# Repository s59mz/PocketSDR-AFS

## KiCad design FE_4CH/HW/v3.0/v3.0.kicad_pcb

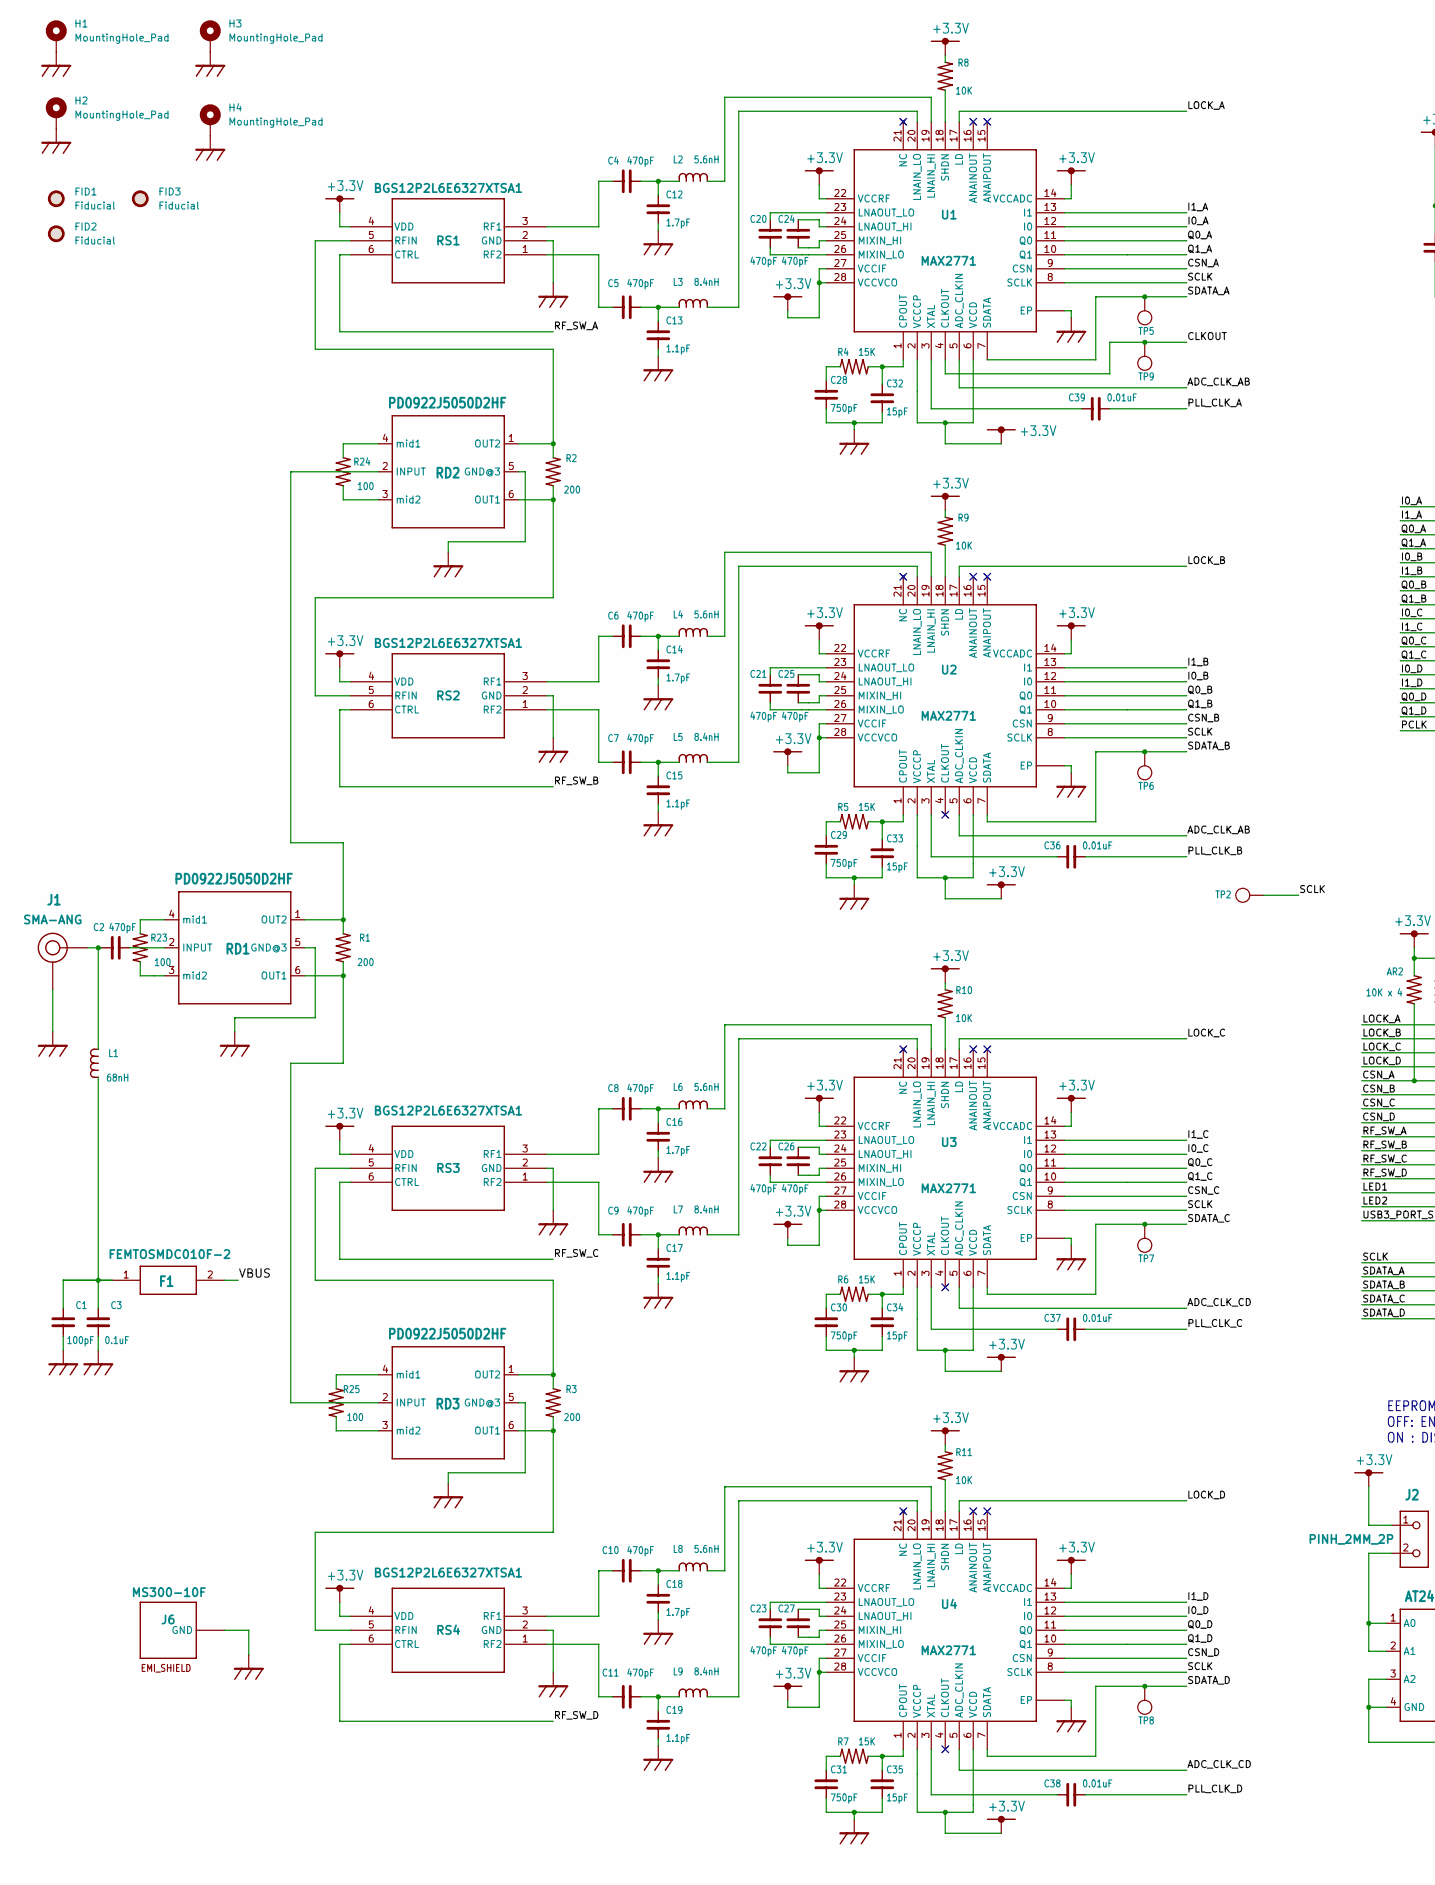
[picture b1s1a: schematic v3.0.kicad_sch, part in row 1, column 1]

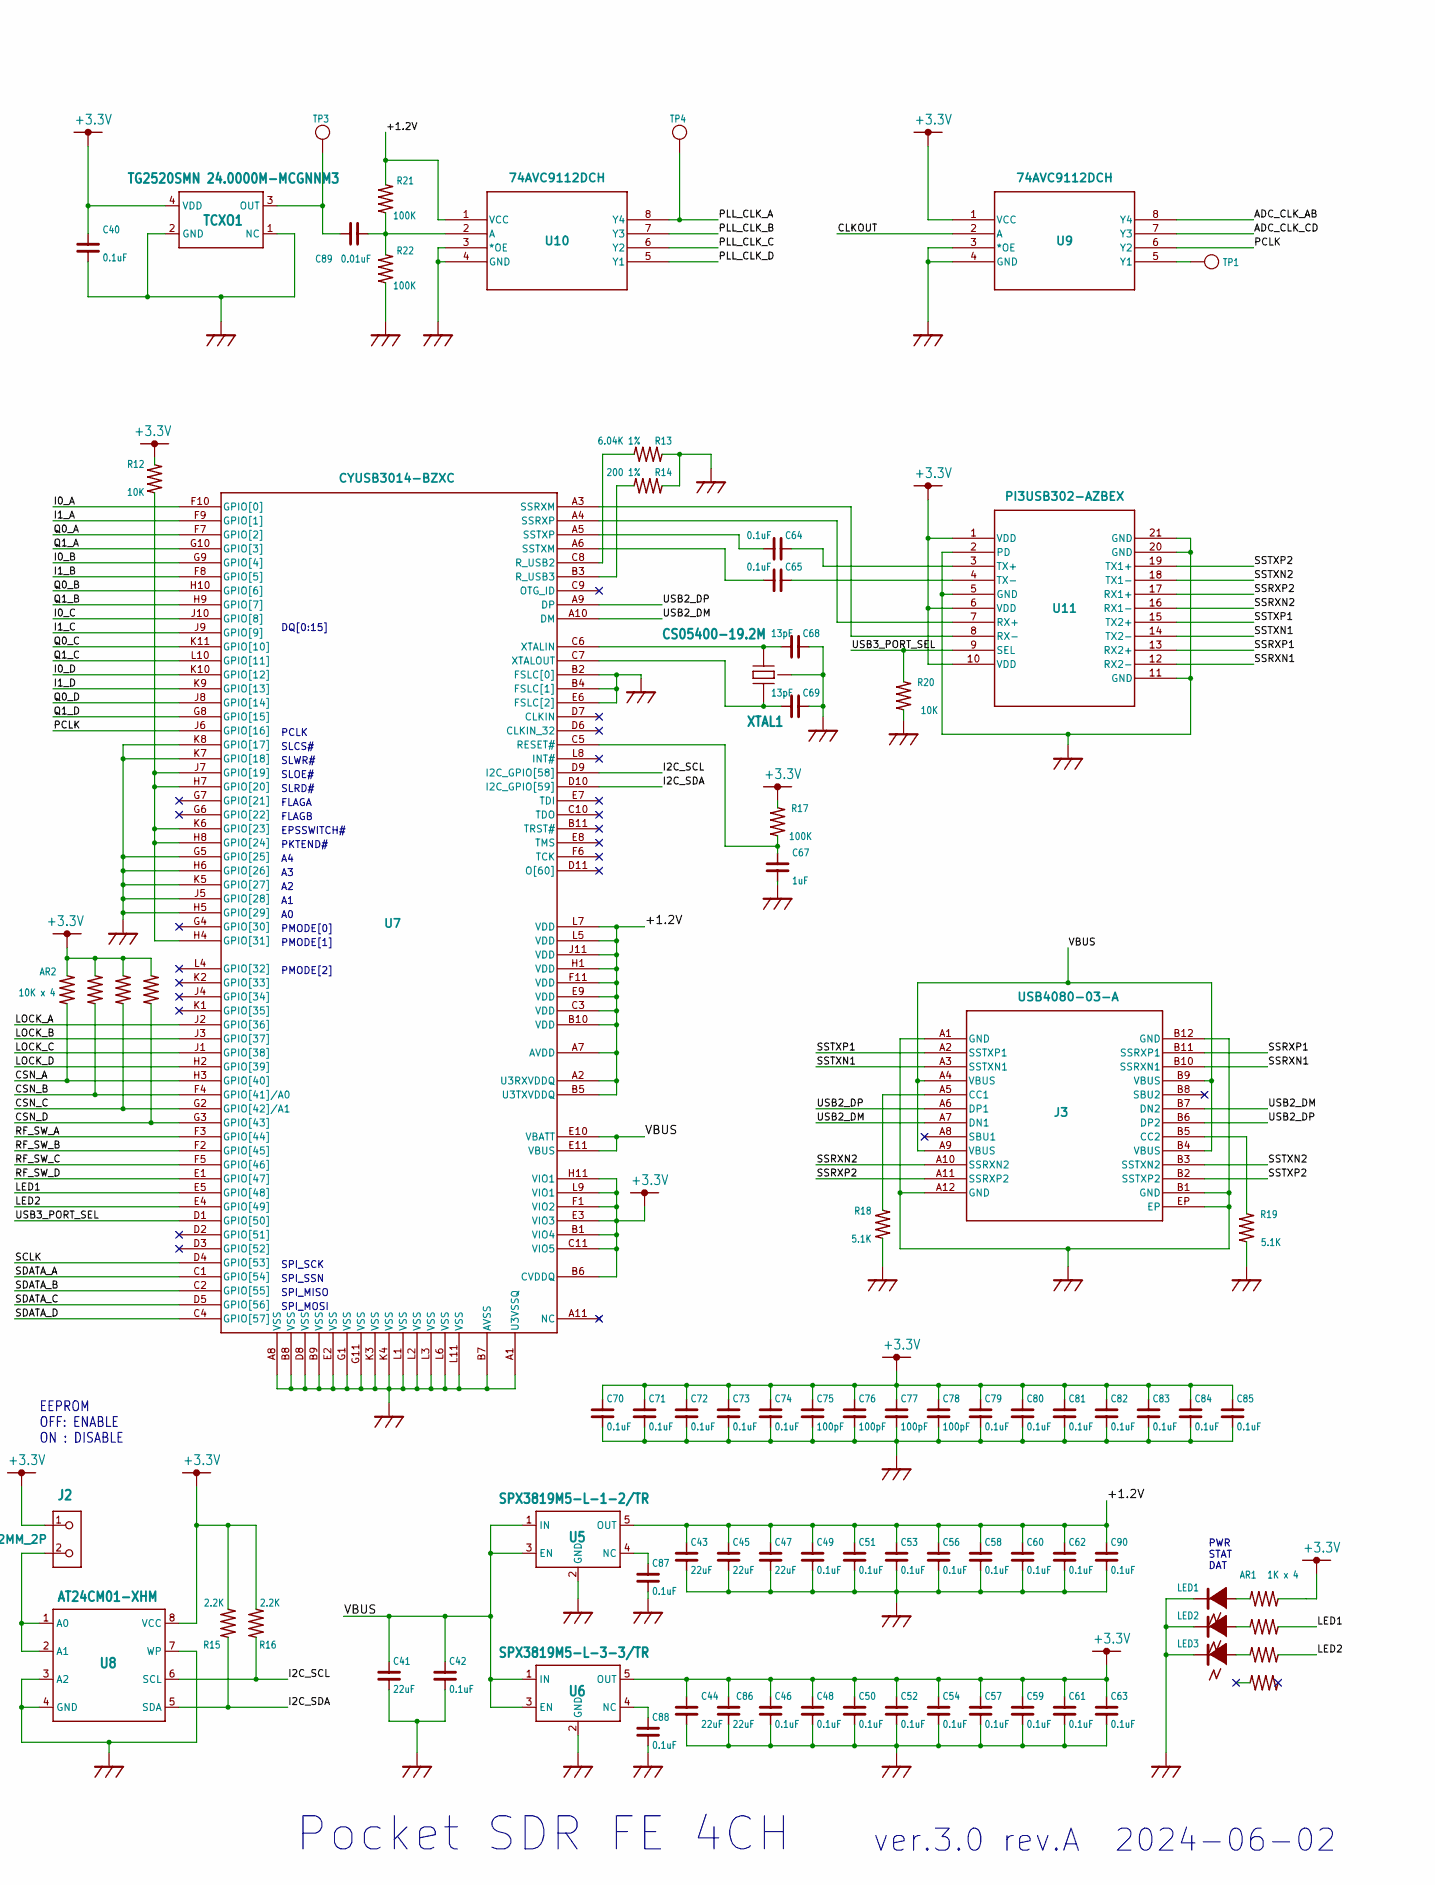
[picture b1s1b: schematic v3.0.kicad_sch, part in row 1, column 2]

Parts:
AR1: 1K x 4; EXB28V
AR2: 10K x 4; EXB28V
C1, C75, C76, C77, C78: 100pF; C1005
C2, C4, C5, C6, C7, C8, C9, C10, C11, C20, C21, C22, C23, C24, C25, C26, C27: 470pF; C1005
C3, C40, C42, C46, C48, C49, C50, C51, C52, C53, C54, C56, C57, C58, C59, C60, C61, C62, C63, C64, C65, C70, C71, C72, C73, C74, C79, C80, C81, C82, C83, C84, C85, C87, C88, C90: 0.1uF; C1005
C12, C14, C16, C18: 1.7pF; C1005
C13, C15, C17, C19: 1.1pF; C1005
C28, C29, C30, C31: 750pF; C1005
C32, C33, C34, C35: 15pF; C1005
C36, C37, C38, C39, C89: 0.01uF; C1005
C41, C43, C44, C45, C47, C86: 22uF; C1608
C67: 1uF; C1005
C68, C69: 13pF; C1005
F1: FEMTOSMDC010F-2; C1608
FID1, FID2, FID3: Fiducial; Fiducial_0.75mm_Mask1.5mm
H1, H2, H3, H4: MountingHole_Pad; MountingHole_2.2mm_M2_DIN965_Pad
J1: SMA-ANG
J2: PINH_2MM_2P; PINH-2MM-2P
J3: USB4080-03-A; USB4080-03-A_GCT
J6: MS300-10F
L1: 68nH; C1608
L2, L4, L6, L8: 5.6nH; C1005
L3, L5, L7, L9: 8.4nH; C1005
LED1, LED2, LED3: LED1608; LED_1608
R1, R2, R3: 200; C1005
R4, R5, R6, R7: 15K; C1005
R8, R9, R10, R11, R12, R20: 10K; C1005
R13: 6.04K 1%; C1005
R14: 200 1%; C1005
R15, R16: 2.2K; C1005
R17, R21, R22: 100K; C1005
R18, R19: 5.1K; C1005
R23, R24, R25: 100; C1005
RD1, RD2, RD3: PD0922J5050D2HF; RF_DIV
RS1, RS2, RS3, RS4: BGS12P2L6E6327XTSA1; PG-TSLP-6-4_INF
TCXO1: TG2520SMN 24.0000M-MCGNNM3; TCXO
TP1, TP2, TP3, TP4, TP5, TP6, TP7, TP8, TP9: TP0.5
U1, U2, U3, U4: MAX2771; TQFN28
U5: SPX3819M5-L-1-2/TR; SOT23
U6: SPX3819M5-L-3-3/TR; SOT23
U7: CYUSB3014-BZXC; BGA-121
U8: AT24CM01-XHM; TSSOP_8P
U9, U10: 74AVC9112DCH; VSSOP8_SOT765-1_NEX
U11: PI3USB302-AZBEX; 20TQFN-ZB_PI3USB302-A_DIO
XTAL1: CS05400-19.2M; XTAL_SMD

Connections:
+3.3V: AR1.2, AR2.2, AR2.4, AR2.6, AR2.8, C40.1, C44.1, C46.1, C48.1, C50.1, C52.1, C54.1, C57.1, C59.1, C61.1, C63.1, C70.1, C71.1, C72.1, C73.1, C74.1, C75.1, C76.1, C77.1, C78.1, C79.1, C80.1, C81.1, C82.1, C83.1, C84.1, C85.1, C86.1, J2.1, R8.2, R9.2, R10.2, R11.2, R12.1, R15.2, R16.2, R17.2, RS1.4 (VDD), RS2.4 (VDD), RS3.4 (VDD), RS4.4 (VDD), TCXO1.4 (VDD), U1.2 (VCCCP), U1.6 (VCCD), U1.14 (VCCADC), U1.22 (VCCRF), U1.27 (VCCIF), U1.28 (VCCVCO), U2.2 (VCCCP), U2.6 (VCCD), U2.14 (VCCADC), U2.22 (VCCRF), U2.27 (VCCIF), U2.28 (VCCVCO), U3.2 (VCCCP), U3.6 (VCCD), U3.14 (VCCADC), U3.22 (VCCRF), U3.27 (VCCIF), U3.28 (VCCVCO), U4.2 (VCCCP), U4.6 (VCCD), U4.14 (VCCADC), U4.22 (VCCRF), U4.27 (VCCIF), U4.28 (VCCVCO), U6.5 (OUT), U7.B1 (VIO4), U7.B6 (CVDDQ), U7.C11 (VIO5), U7.E3 (VIO3), U7.F1 (VIO2), U7.H11 (VIO1), U7.L9 (VIO1), U8.8 (VCC), U9.1 (VCC), U11.1 (VDD), U11.6 (VDD), U11.10 (VDD)
/+1.2V: C43.1, C45.1, C47.1, C49.1, C51.1, C53.1, C56.1, C58.1, C60.1, C62.1, C90.1, R21.1, U5.5 (OUT), U7.A2 (U3RXVDDQ), U7.A7 (AVDD), U7.B5 (U3TXVDDQ), U7.B10 (VDD), U7.C3 (VDD), U7.E9 (VDD), U7.F11 (VDD), U7.H1 (VDD), U7.J11 (VDD), U7.L5 (VDD), U7.L7 (VDD), U10.1 (VCC)
/ADC_CLK_AB: U1.5 (ADC_CLKIN), U2.5 (ADC_CLKIN), U9.8 (Y4)
/ADC_CLK_CD: U3.5 (ADC_CLKIN), U4.5 (ADC_CLKIN), U9.7 (Y3)
/CLKOUT: TP9.1, U1.4 (CLKOUT), U9.2 (A)
/CSN_A: AR2.1, U1.9 (CSN), U7.H3 (GPIO[40])
/CSN_B: AR2.3, U2.9 (CSN), U7.F4 (GPIO[41]/A0)
/CSN_C: AR2.5, U3.9 (CSN), U7.G2 (GPIO[42]/A1)
/CSN_D: AR2.7, U4.9 (CSN), U7.G3 (GPIO[43])
/I0_A: U1.12 (I0), U7.F10 (GPIO[0])
/I0_B: U2.12 (I0), U7.G9 (GPIO[4])
/I0_C: U3.12 (I0), U7.J10 (GPIO[8])
/I0_D: U4.12 (I0), U7.K10 (GPIO[12])
/I1_A: U1.13 (I1), U7.F9 (GPIO[1])
/I1_B: U2.13 (I1), U7.F8 (GPIO[5])
/I1_C: U3.13 (I1), U7.J9 (GPIO[9])
/I1_D: U4.13 (I1), U7.K9 (GPIO[13])
/I2C_SCL: R16.1, U7.D9 (I2C_GPIO[58]), U8.6 (SCL)
/I2C_SDA: R15.1, U7.D10 (I2C_GPIO[59]), U8.5 (SDA)
/LED1: AR1.4, U7.E5 (GPIO[48])
/LED2: AR1.6, U7.E4 (GPIO[49])
/LOCK_A: U1.17 (LD), U7.J2 (GPIO[36])
/LOCK_B: U2.17 (LD), U7.J3 (GPIO[37])
/LOCK_C: U3.17 (LD), U7.J1 (GPIO[38])
/LOCK_D: U4.17 (LD), U7.H2 (GPIO[39])
/PCLK: U7.J6 (GPIO[16]), U9.6 (Y2)
/PLL_CLK_A: C39.1, TP4.1, U10.8 (Y4)
/PLL_CLK_B: C36.1, U10.7 (Y3)
/PLL_CLK_C: C37.1, U10.6 (Y2)
/PLL_CLK_D: C38.1, U10.5 (Y1)
/Q0_A: U1.11 (Q0), U7.F7 (GPIO[2])
/Q0_B: U2.11 (Q0), U7.H10 (GPIO[6])
/Q0_C: U3.11 (Q0), U7.K11 (GPIO[10])
/Q0_D: U4.11 (Q0), U7.J8 (GPIO[14])
/Q1_A: U1.10 (Q1), U7.G10 (GPIO[3])
/Q1_B: U2.10 (Q1), U7.H9 (GPIO[7])
/Q1_C: U3.10 (Q1), U7.L10 (GPIO[11])
/Q1_D: U4.10 (Q1), U7.G8 (GPIO[15])
/RF_SW_A: RS1.6 (CTRL), U7.F3 (GPIO[44])
/RF_SW_B: RS2.6 (CTRL), U7.F2 (GPIO[45])
/RF_SW_C: RS3.6 (CTRL), U7.F5 (GPIO[46])
/RF_SW_D: RS4.6 (CTRL), U7.E1 (GPIO[47])
/SCLK: TP2.1, U1.8 (SCLK), U2.8 (SCLK), U3.8 (SCLK), U4.8 (SCLK), U7.D4 (GPIO[53])
/SDATA_A: TP5.1, U1.7 (SDATA), U7.C1 (GPIO[54])
/SDATA_B: TP6.1, U2.7 (SDATA), U7.C2 (GPIO[55])
/SDATA_C: TP7.1, U3.7 (SDATA), U7.D5 (GPIO[56])
/SDATA_D: TP8.1, U4.7 (SDATA), U7.C4 (GPIO[57])
/SSRXN1: J3.B10 (SSRXN1), U11.12 (RX2-)
/SSRXN2: J3.A10 (SSRXN2), U11.16 (RX1-)
/SSRXP1: J3.B11 (SSRXP1), U11.13 (RX2+)
/SSRXP2: J3.A11 (SSRXP2), U11.17 (RX1+)
/SSTXN1: J3.A3 (SSTXN1), U11.14 (TX2-)
/SSTXN2: J3.B3 (SSTXN2), U11.18 (TX1-)
/SSTXP1: J3.A2 (SSTXP1), U11.15 (TX2+)
/SSTXP2: J3.B2 (SSTXP2), U11.19 (TX1+)
/USB2_DM: J3.A7 (DN1), J3.B7 (DN2), U7.A10 (DM)
/USB2_DP: J3.A6 (DP1), J3.B6 (DP2), U7.A9 (DP)
/USB3_PORT_SEL: R20.2, U7.D1 (GPIO[50]), U11.9 (SEL)
/VBUS: C41.1, C42.1, F1.2, J3.A4 (VBUS), J3.A9 (VBUS), J3.B4 (VBUS), J3.B9 (VBUS), U5.1 (IN), U5.3 (EN), U6.1 (IN), U6.3 (EN), U7.E10 (VBATT), U7.E11 (VBUS)
GND: C1.1, C3.1, C12.1, C13.1, C14.1, C15.1, C16.1, C17.1, C18.1, C19.1, C28.2, C29.2, C30.2, C31.2, C32.2, C33.2, C34.2, C35.2, C40.2, C41.2, C42.2, C43.2, C44.2, C45.2, C46.2, C47.2, C48.2, C49.2, C50.2, C51.2, C52.2, C53.2, C54.2, C56.2, C57.2, C58.2, C59.2, C60.2, C61.2, C62.2, C63.2, C67.2, C68.1, C69.1, C70.2, C71.2, C72.2, C73.2, C74.2, C75.2, C76.2, C77.2, C78.2, C79.2, C80.2, C81.2, C82.2, C83.2, C84.2, C85.2, C86.2, C87.2, C88.2, C90.2, H1.1, H2.1, H3.1, H4.1, J1.P2 (GND), J1.P3 (GND), J1.P4 (GND), J1.P5 (GND), J3.A1 (GND), J3.A12 (GND), J3.B1 (GND), J3.B12 (GND), J3.EP, J6.P1 (GND), LED1.2, LED2.2, LED3.2, R13.1, R14.1, R18.1, R19.1, R20.1, R22.2, RD1.5 (GND@3), RD2.5 (GND@3), RD3.5 (GND@3), RS1.2 (GND), RS2.2 (GND), RS3.2 (GND), RS4.2 (GND), TCXO1.1 (NC), TCXO1.2 (GND), U1.C1 (EP), U1.C2 (EP), U1.C3 (EP), U1.C4 (EP), U1.EP, U1.V1 (EP), U1.V2 (EP), U1.V3 (EP), U1.V4 (EP), U1.V5 (EP), U1.V6 (EP), U1.V7 (EP), U1.V8 (EP), U1.V9 (EP), U2.C1 (EP), U2.C2 (EP), U2.C3 (EP), U2.C4 (EP), U2.EP, U2.V1 (EP), U2.V2 (EP), U2.V3 (EP), U2.V4 (EP), U2.V5 (EP), U2.V6 (EP), U2.V7 (EP), U2.V8 (EP), U2.V9 (EP), U3.C1 (EP), U3.C2 (EP), U3.C3 (EP), U3.C4 (EP), U3.EP, U3.V1 (EP), U3.V2 (EP), U3.V3 (EP), U3.V4 (EP), U3.V5 (EP), U3.V6 (EP), U3.V7 (EP), U3.V8 (EP), U3.V9 (EP), U4.C1 (EP), U4.C2 (EP), U4.C3 (EP), U4.C4 (EP), U4.EP, U4.V1 (EP), U4.V2 (EP), U4.V3 (EP), U4.V4 (EP), U4.V5 (EP), U4.V6 (EP), U4.V7 (EP), U4.V8 (EP), U4.V9 (EP), U5.2 (GND), U6.2 (GND), U7.A1 (U3VSSQ), U7.A8 (VSS), U7.B2 (FSLC[0]), U7.B4 (FSLC[1]), U7.B7 (AVSS), U7.B8 (VSS), U7.B9 (VSS), U7.D8 (VSS), U7.E2 (VSS), U7.E6 (FSLC[2]), U7.G1 (VSS), U7.G5 (GPIO[25]), U7.G11 (VSS), U7.H5 (GPIO[29]), U7.H6 (GPIO[26]), U7.J5 (GPIO[28]), U7.K3 (VSS), U7.K4 (VSS), U7.K5 (GPIO[27]), U7.K7 (GPIO[18]), U7.K8 (GPIO[17]), U7.L1 (VSS), U7.L2 (VSS), U7.L3 (VSS), U7.L6 (VSS), U7.L11 (VSS), U8.3 (A2), U8.4 (GND), U8.7 (WP), U9.3 (*OE), U9.4 (GND), U10.3 (*OE), U10.4 (GND), U11.2 (PD), U11.5 (GND), U11.11 (GND), U11.20 (GND), U11.21 (GND), XTAL1.P2 (GND), XTAL1.P4 (GND)
unnamed: AR1.1, LED1.1 (+)
unnamed: AR1.3, LED2.1 (+)
unnamed: AR1.5, LED3.1 (+)
unnamed: C1.2, C3.2, F1.1, L1.1
unnamed: C2.1, J1.P1 (RF), L1.2
unnamed: J2.2, U8.1 (A0), U8.2 (A1)
unnamed: J3.A5 (CC1), R18.2
unnamed: J3.B5 (CC2), R19.2
unnamed: C4.2, C12.2, L2.1
unnamed: L2.2, U1.19 (LNAIN_HI)
unnamed: C5.2, C13.2, L3.1
unnamed: L3.2, U1.20 (LNAIN_LO)
unnamed: C6.2, C14.2, L4.1
unnamed: L4.2, U2.19 (LNAIN_HI)
unnamed: C7.2, C15.2, L5.1
unnamed: L5.2, U2.20 (LNAIN_LO)
unnamed: C8.2, C16.2, L6.1
unnamed: L6.2, U3.19 (LNAIN_HI)
unnamed: C9.2, C17.2, L7.1
unnamed: L7.2, U3.20 (LNAIN_LO)
unnamed: C10.2, C18.2, L8.1
unnamed: L8.2, U4.19 (LNAIN_HI)
unnamed: C11.2, C19.2, L9.1
unnamed: L9.2, U4.20 (LNAIN_LO)
unnamed: R1.1, RD1.6 (OUT1), RD3.2 (INPUT)
unnamed: R1.2, RD1.1 (OUT2), RD2.2 (INPUT)
unnamed: R2.1, RD2.6 (OUT1), RS2.5 (RFIN)
unnamed: R2.2, RD2.1 (OUT2), RS1.5 (RFIN)
unnamed: R3.1, RD3.6 (OUT1), RS4.5 (RFIN)
unnamed: R3.2, RD3.1 (OUT2), RS3.5 (RFIN)
unnamed: C28.1, R4.1
unnamed: C32.1, R4.2, U1.1 (CPOUT)
unnamed: C29.1, R5.1
unnamed: C33.1, R5.2, U2.1 (CPOUT)
unnamed: C30.1, R6.1
unnamed: C34.1, R6.2, U3.1 (CPOUT)
unnamed: C31.1, R7.1
unnamed: C35.1, R7.2, U4.1 (CPOUT)
unnamed: R8.1, U1.18 (SHDN)
unnamed: R9.1, U2.18 (SHDN)
unnamed: R10.1, U3.18 (SHDN)
unnamed: R11.1, U4.18 (SHDN)
unnamed: R12.2, U7.H4 (GPIO[31]), U7.H7 (GPIO[20]), U7.H8 (GPIO[24]), U7.J7 (GPIO[19]), U7.K6 (GPIO[23])
unnamed: R13.2, U7.C8 (R_USB2)
unnamed: R14.2, U7.B3 (R_USB3)
unnamed: C67.1, R17.1, U7.C5 (RESET#)
unnamed: C89.2, R21.2, R22.1, U10.2 (A)
unnamed: R23.1, RD1.3 (mid2)
unnamed: R23.2, RD1.4 (mid1)
unnamed: R24.1, RD2.3 (mid2)
unnamed: R24.2, RD2.4 (mid1)
unnamed: R25.1, RD3.3 (mid2)
unnamed: R25.2, RD3.4 (mid1)
unnamed: C2.2, RD1.2 (INPUT)
unnamed: C4.1, RS1.3 (RF1)
unnamed: C5.1, RS1.1 (RF2)
unnamed: C6.1, RS2.3 (RF1)
unnamed: C7.1, RS2.1 (RF2)
unnamed: C8.1, RS3.3 (RF1)
unnamed: C9.1, RS3.1 (RF2)
unnamed: C10.1, RS4.3 (RF1)
unnamed: C11.1, RS4.1 (RF2)
unnamed: C89.1, TCXO1.3 (OUT), TP3.1
unnamed: C24.1, U1.24 (LNAOUT_HI)
unnamed: C20.1, U1.23 (LNAOUT_LO)
unnamed: C24.2, U1.25 (MIXIN_HI)
unnamed: C20.2, U1.26 (MIXIN_LO)
unnamed: C39.2, U1.3 (XTAL)
unnamed: C25.1, U2.24 (LNAOUT_HI)
unnamed: C21.1, U2.23 (LNAOUT_LO)
unnamed: C25.2, U2.25 (MIXIN_HI)
unnamed: C21.2, U2.26 (MIXIN_LO)
unnamed: C36.2, U2.3 (XTAL)
unnamed: C26.1, U3.24 (LNAOUT_HI)
unnamed: C22.1, U3.23 (LNAOUT_LO)
unnamed: C26.2, U3.25 (MIXIN_HI)
unnamed: C22.2, U3.26 (MIXIN_LO)
unnamed: C37.2, U3.3 (XTAL)
unnamed: C27.1, U4.24 (LNAOUT_HI)
unnamed: C23.1, U4.23 (LNAOUT_LO)
unnamed: C27.2, U4.25 (MIXIN_HI)
unnamed: C23.2, U4.26 (MIXIN_LO)
unnamed: C38.2, U4.3 (XTAL)
unnamed: C87.1, U5.4 (NC)
unnamed: C88.1, U6.4 (NC)
unnamed: C65.2, U7.A6 (SSTXM)
unnamed: C64.2, U7.A5 (SSTXP)
unnamed: C68.2, U7.C6 (XTALIN), XTAL1.P1 (XTAL1)
unnamed: C69.2, U7.C7 (XTALOUT), XTAL1.P3 (XTAL2)
unnamed: TP1.1, U9.5 (Y1)
unnamed: U7.A4 (SSRXP), U11.7 (RX+)
unnamed: U7.A3 (SSRXM), U11.8 (RX-)
unnamed: C64.1, U11.3 (TX+)
unnamed: C65.1, U11.4 (TX-)

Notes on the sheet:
PCLK
EPSSWITCH#
SPI_SSN
PMODE[1]
DQ[0:15]
Pocket SDR FE 4CH
PMODE[0]
EEPROM OFF: ENABLE ON : DISABLE
SPI_SCK
SPI_MOSI
SLRD#
SLOE#
SLCS#
PMODE[2]
PWR STAT DAT
SLWR#
PKTEND#
ver.3.0 rev.A 2024-06-02
SPI_MISO
FLAGA
FLAGB

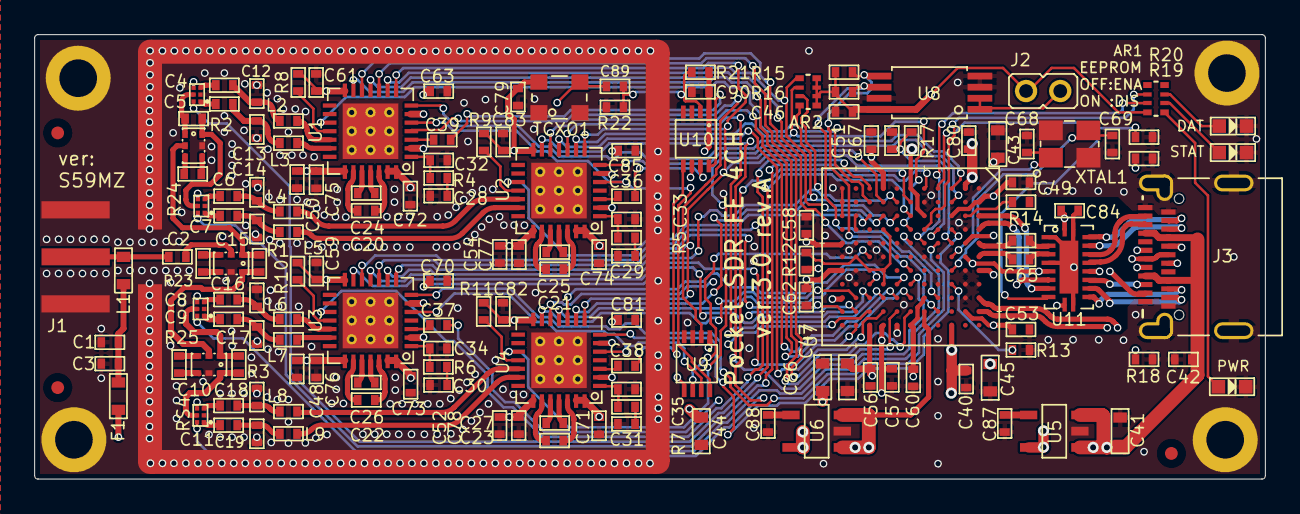
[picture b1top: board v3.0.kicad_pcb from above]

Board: 4 copper layers, 72.0 x 26.0 mm, 168 parts (0 on the bottom side), 154 nets.

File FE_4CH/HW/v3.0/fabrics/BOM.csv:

reference,value,footprint,MPN,manufacturer,Category,SKU,price,quantity,"Procurement Type"
AR1,1K x 4,EXB28V,EXB28V102JX,Panasonic,Resistor Arrays,2500410648,0.0157,1
AR2,10K x 4,EXB28V,EXB28V103JX,Panasonic,Resistors,1002046491,0.01788,1
"C7,C6,C24,C21,C23,C10,C20,C8,C2,C25,C9,C11,C4,C22,C27,C26,C5",470pF,C1005,04025A471JAT2A,Kyocera,Ceramic Capacitors,1007334786,0.00692,17
"C13,C15,C17,C19",1.1pF,C1005,0402N1R0B500CT,Walsin Technologies,Ceramic Capacitors,1002639598,0.00196,4
"C16,C18,C12,C14",1.7pF,C1005,0402N1R5B500CT,Walsin Technologies,Ceramic Capacitors,2500327638,0.00174,4
"C31,C28,C29,C30",750pF,C1005,0402B821K500CT,Walsin Technologies,Ceramic Capacitors,2500244080,0.00244,4
"C32,C33,C34,C35",15pF,C1005,0402N150J500CT,Walsin Technologies,Ceramic Capacitors,1003461157,0.00111,4
"C38,C36,C39,C89,C37",0.01uF,C1005,TMK105B7103KV-F,Taiyo Yuden,Ceramic Capacitors,1010036440,0.00196,5
"C44,C47,C41,C45,C86,C43",22uF,C1608,CL10A226MP8NUNE,Samsung,Ceramic Capacitors,2500215887,0.00913,6
"C50,C57,C40,C59,C60,C65,C85,C82,C54,C42,C62,C56,C81,C83,C48,C53,C79,C74,C90,C63,C73,C84,C52,C3,C87,C70,C46,C72,C49,C51,C58,C71,C64,C80,C61,C88",0.1uF,C1005,LMK105BJ104KV-F,Taiyo Yuden,Ceramic Capacitors,1003461391,0.00226,36
C67,1uF,C1005,TMK105BJ105KV-F,Taiyo Yuden,Ceramic Capacitors,2500239815,0.00435,1
"C69,C68",13pF,C1005,0402N120J500CT,Walsin Technologies,Ceramic Capacitors,1002717966,0.00114,2
"C77,C75,C76,C78,C1",100pF,C1005,0402B101K500CT,Walsin Technologies,Ceramic Capacitors,1003073423,0.00115,5
F1,FEMTOSMDC010F-2,C1608,FEMTOSMDC010F-2,Littelfuse,PTC Resettable Fuses,1009923857,0.39562,1
J1,SMA-ANG,SMA-ANG,HJ-SMA716,HJ,RF / Coaxial Connectors,1012647363,0.77735,1
J2,PINH_2MM_2P,PINH-2MM-2P,X4611WV-02I-C40D28,XKB,Connectors,2500393555,0.01332,1
J3,USB4080-03-A,USB4080-03-A_GCT,TYPEC-324G-BCP24,XUNPU,Universal,2500406871,0.31515,1
J6,MS300-10F,MS300-10F,MS300-10F,MASACH,Tools and Supplies,-,-,1
L1,68nH,C1608,SDCL1608C68NJTDF,Sunlord Electronics,Fixed Inductors,2500331116,0.00645,1
"L6,L2,L4,L8",5.6nH,C1005,SDCL1005C5N6STDF,Sunlord Electronics,Fixed Inductors,2500330509,0.00191,4
"L9,L7,L3,L5",8.4nH,C1005,MLG1005S8N2HT000,TDK,Fixed Inductors,1000509089,0.00785,4
"LED2,LED1",LED1608,LED_1608,XL-1608UGC-04,XINGLIGHT,LEDs,2500325200,0.00342,2
LED3,LED1608,LED_1608,XL-1608SURC-06,XINGLIGHT,LEDs,2500413843,0.0028,1
"R3,R2,R1",200,C1005,AC0402JR-07200RL,Yageo,Chip SMD Resistors,2500274293,0.00074,3
"R6,R5,R7,R4",15K,C1005,CR0402-FX-1502GLF,Bourns,Chip SMD Resistors,1043497899,0.00908,4
"R9,R10,R11,R12,R20,R8",10K,C1005,MCR01MRTF1002,Rohm,Chip SMD Resistors,1013970158,0.00343,6
R13,6.04K 1%,C1005,RK73H1ETTP6041F,KOA,Chip SMD Resistors,2500421777,0.00269,1
R14,200 1%,C1005,AC0402JR-07200RL,Yageo,Chip SMD Resistors,2500274293,0.00074,1
"R16,R15",2.2K,C1005,CRCW04022K20JNED,Vishay,Chip SMD Resistors,1027919991,0.00345,2
"R19,R18",5.1K,C1005,CR0402-FX-5101GLF,Bourns,Chip SMD Resistors,1043100135,0.0048,2
"R22,R17,R21",100K,C1005,CRCW0402100KFKED,Vishay,Chip SMD Resistors,2500013817,0.00188,3
"R23,R25,R24",100,C1005,RC0402FR-07100RL,Yageo,Chip SMD Resistors,2500015778,0.00039,3
"RD1,RD2,RD3",PD0922J5050D2HF,RF_DIV,PD0922J5050D2HF,TTM Technologies,"Signal Buffers, Repeaters, Splitters",-,-,3
"RS1,RS2,RS4,RS3",BGS12P2L6E6327XTSA1,PG-TSLP-6-4_INF,BGS12P2L6E6327XTSA1,Infineon,RF Semiconductors and Devices,2500422484,0.30715,4
TCXO1,TG2520SMN 24.0000M-MCGNNM3,TCXO,ECS-TXO-2520MV-240-AN-TR,ECS International,Oscillators,1009927745,4.35675,1
U1,MAX2771,TQFN28,MAX2771ETI+,Analog Devices,"RF Receivers, Transceivers",1043509960,208.69204,1,DNP
U2,MAX2771,TQFN28,MAX2771ETI+,Analog Devices,"RF Receivers, Transceivers",1043509960,208.69204,1,DNP
U3,MAX2771,TQFN28,MAX2771ETI+,Analog Devices,"RF Receivers, Transceivers",1043509960,208.69204,1,DNP
U4,MAX2771,TQFN28,MAX2771ETI+,Analog Devices,"RF Receivers, Transceivers",1043509960,208.69204,1,DNP
U5,SPX3819M5-L-1-2/TR,SOT23,SPX3819M5-L-1-2/TR,Maxlinear,"Linear Voltage Regulators, LDO",2500407307,0.20034,1
U6,SPX3819M5-L-3-3/TR,SOT23,SPX3819M5-L-3-3/TR,Maxlinear,"Linear Voltage Regulators, LDO",2500406992,0.12897,1
U7,CYUSB3014-BZXC,BGA-121,CYUSB3014-BZXC,Infineon,Microcontrollers,1010536216,12.34859,1
U8,AT24CM01-XHM,TSSOP_8P,AT24CM01-SSHD-T,Microchip Technology,EEPROM,2500408584,0.81856,1
"U9,U10",74AVC9112DCH,VSSOP8_SOT765-1_NEX,74AVC9112DCH,Nexperia,"Drivers, Receivers, Transceivers",-,-,2
U11,PI3USB302-AZBEX,20TQFN-ZB_PI3USB302-A_DIO,PI3USB302-AZBEX,Diodes,"Analog Switches, Multiplexers and Demultiplexers",2500410216,0.67269,1
XTAL1,CS05400-19.2M,XTAL_SMD,XYOBCLNANF-19.2MHz,Taitien Electronics,Crystals,2500244502,0.07998,1

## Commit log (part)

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2026-01-03 replace wilkinson splitter with double, add mounting holes and fidushes
